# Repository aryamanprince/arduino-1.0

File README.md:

Files to be submitted for Zine robotics and research group interview

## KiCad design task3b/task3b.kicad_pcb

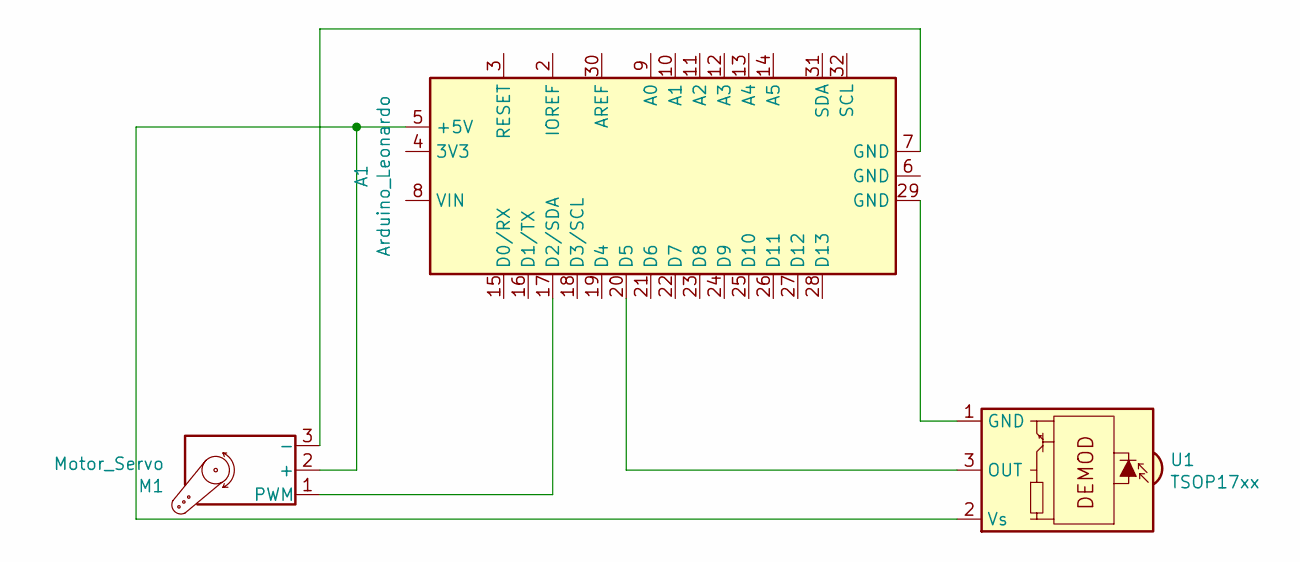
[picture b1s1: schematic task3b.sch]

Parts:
A1: Arduino_Leonardo; PinSocket_1x32_P2.54mm_Vertical_SMD_Pin1Left
M1: Motor_Servo
U1: TSOP17xx; Vishay_CAST-3Pin

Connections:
unnamed: A1.5 (+5V), M1.2 (+), U1.2 (Vs)
unnamed: A1.7 (GND), M1.3 (-)
unnamed: A1.17 (D2/SDA), M1.1 (PWM)
unnamed: A1.20 (D5), U1.3 (OUT)
unnamed: A1.29 (GND), U1.1 (GND)

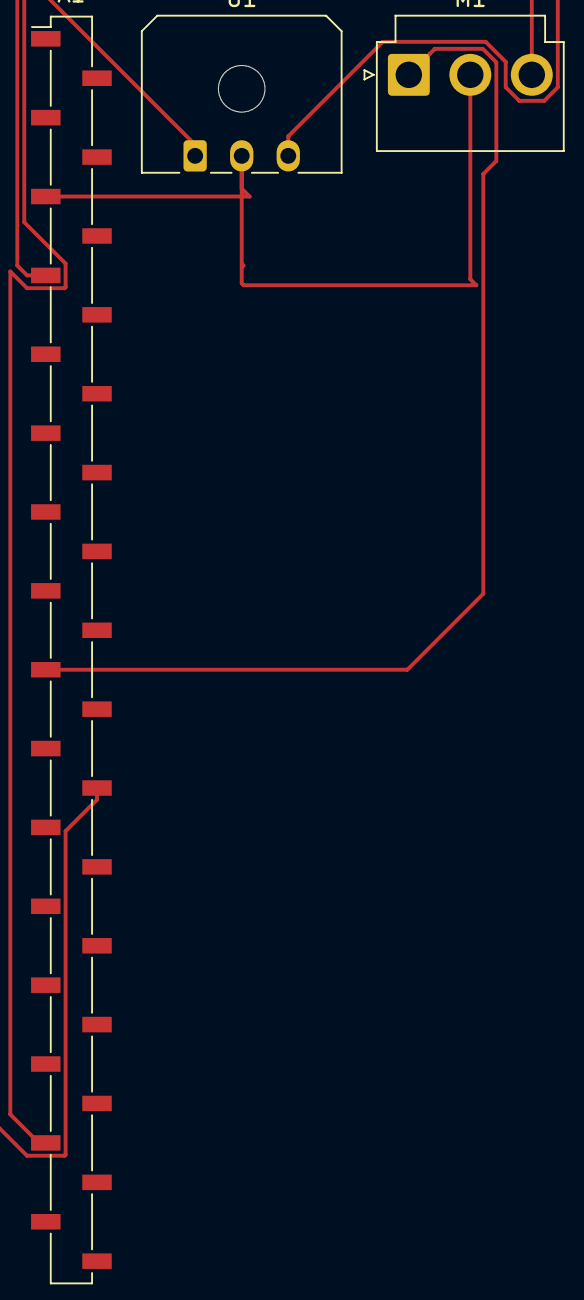
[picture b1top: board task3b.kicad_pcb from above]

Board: 2 copper layers, 3 parts (0 on the bottom side), 5 nets.
